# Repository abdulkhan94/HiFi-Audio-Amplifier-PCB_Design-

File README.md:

# Transparent HiFi Audio Amplifier for Headphones
## Introduction
The goal of our Transparent HiFi USB Audio Amplifier system is to take in a audio signal via USB, allow the user to modify amplifier and volume controls, and to hear the modified audio signal through headphones. Our system specifications are for our design to not produce a DC offset that’s greater than 20mV, to not produce excessive power spikes greater than 50mV, have an output impedance of less than 2 ohms, and to support 8 specific headphones with a range of impedances from 16 to 600 ohms. The left and right audio signals must have flat frequency responses (+/-2.5dB), linear/flat phase responses without being set at 0dB, noise under -105dBv (-103dBu) and distortion under 1% THd into 150 ohms at 1Vrms. Lastly, the power amplifier must have a slew of under 3V/us by a square wave of 600 ohms. 

## Power Amplifier
The power amplifier subsystem will get a 1 V pk-pk signal input from the Amplifier controls subsystem and will amplify that to output analog audio signal across various headphones. All parts of the subsystem will be powered by +13/-13 DC Voltage signal. The subsystem consists of two different parts to achieve amplification of both current and voltage.
The first stage of the design consists of a preamplifier design. This is essentially a Class A audio amplifier which is implemented in order to boost the voltage of the 1 V pk-pk signal that the subsystem receives as input from the amplifier controls subsystem. A major design consideration that has been made here revolves around amplifying voltage to the adequate level while maintaining low noise in the signal. The design consists of two biasing resistors followed by a NPN transistor. This part of the design is powered by a +13V DC power rail. 
The next step of the design consists of the power amplifier which amplifies the current. This part of the subsystem is required to have enough current in order to drive the output across the headphones. A class AB amplifier design has been implemented here in order to achieve the adequate current amplification. This design also consists of two biasing resistors for each transistor and is powered by +/- 13V DC power rails.

## Current Status
* All subsytems of the design have been finalised and layed out on PCB's. 
* All subsystems integrated and fully functional.

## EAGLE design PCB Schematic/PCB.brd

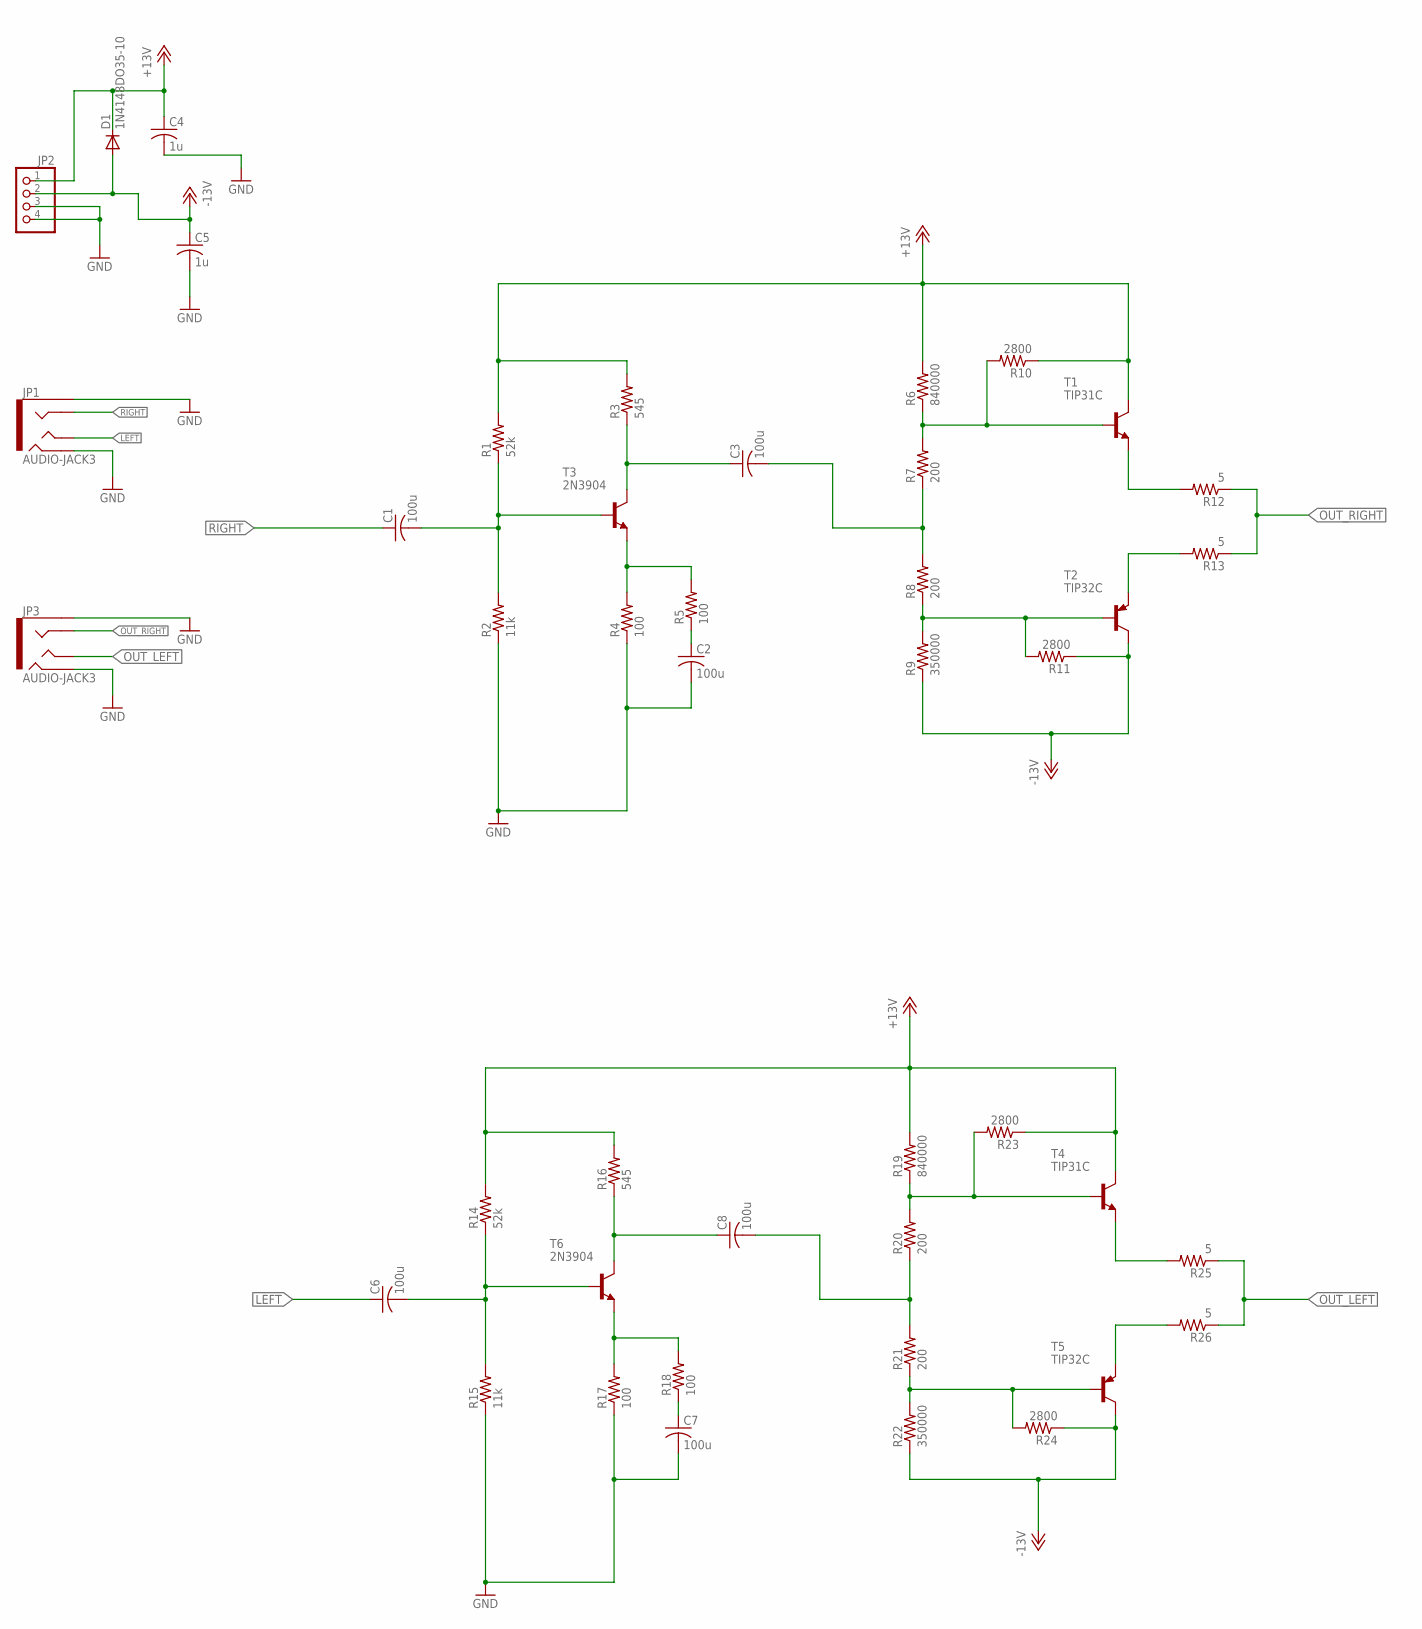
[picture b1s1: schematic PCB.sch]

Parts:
C1, C2, C3, C6, C7, C8: 100u; C025-024X044
C4, C5: 1u; C025-024X044
D1: 1N4148DO35-10; DO35-10
JP1, JP3: AUDIO-JACK3; AUDIO-JACK-TRRS-SMD
JP2: PINHD-1X4; 1X04
R1, R14: 52k; 0204V
R2, R15: 11k; 0204V
R3, R16: 545; 0204V
R4, R5, R17, R18: 100; 0204V
R6, R19: 840000; 0204V
R7, R8, R20, R21: 200; 0204V
R9, R22: 350000; 0204V
R10, R11, R23, R24: 2800; 0204V
R12, R13, R25, R26: 5; 0204V
T1, T4: TIP31C; TO220
T2, T5: TIP32C; TO220
T3, T6: 2N3904; TO92

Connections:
+13V: C4.1, D1.C, JP2.1, R1.2, R3.2, R6.2, R10.1, R14.2, R16.2, R19.2, R23.1, T1.2 (C), T4.2 (C)
-13V: C5.1, D1.A, JP2.2, R9.1, R11.1, R22.1, R24.1, T2.2 (C), T5.2 (C)
GND: C2.2, C4.2, C5.2, C7.2, JP1.EARTH, JP1.RING2, JP2.3, JP2.4, JP3.EARTH, JP3.RING2, R2.1, R4.1, R15.1, R17.1
LEFT: C6.1, JP1.TIP
unnamed: C1.2, R1.1, R2.2, T3.2 (B)
unnamed: C3.1, R3.1, T3.1 (C)
unnamed: C6.2, R14.1, R15.2, T6.2 (B)
unnamed: R4.2, R5.2, T3.3 (E)
unnamed: R6.1, R7.2, R10.2, T1.1 (B)
unnamed: C2.1, R5.1
unnamed: C3.2, R7.1, R8.2
unnamed: R8.1, R9.2, R11.2, T2.1 (B)
unnamed: R12.2, T1.3 (E)
unnamed: R13.2, T2.3 (E)
unnamed: C8.1, R16.1, T6.1 (C)
unnamed: R17.2, R18.2, T6.3 (E)
unnamed: C7.1, R18.1
unnamed: R19.1, R20.2, R23.2, T4.1 (B)
unnamed: C8.2, R20.1, R21.2
unnamed: R21.1, R22.2, R24.2, T5.1 (B)
unnamed: R25.2, T4.3 (E)
unnamed: R26.2, T5.3 (E)
OUT_LEFT: JP3.TIP, R25.1, R26.1
OUT_RIGHT: JP3.RING1, R12.1, R13.1
RIGHT: C1.1, JP1.RING1

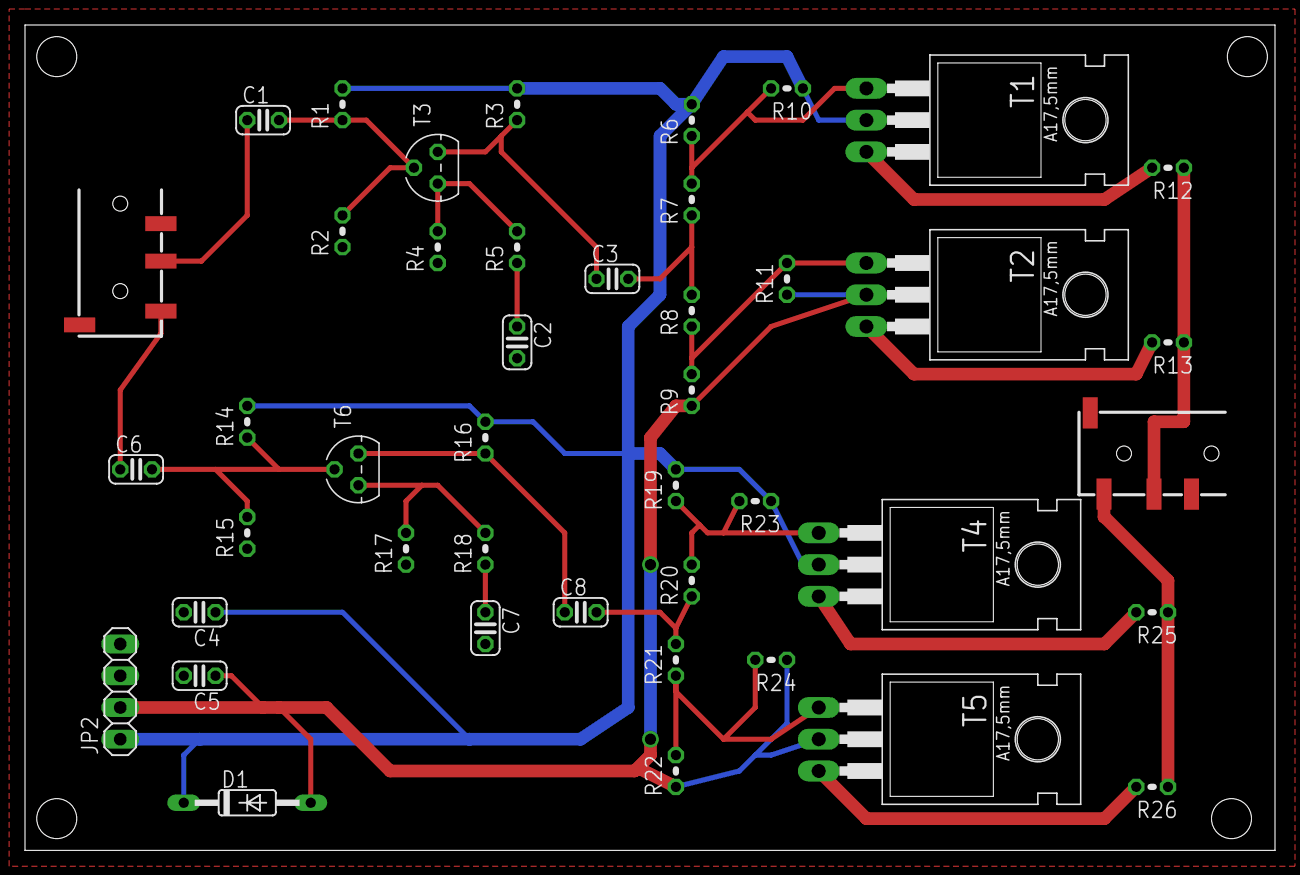
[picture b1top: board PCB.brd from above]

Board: 2 copper layers, 100.0 x 66.0 mm, 44 parts (0 on the bottom side), 25 nets.

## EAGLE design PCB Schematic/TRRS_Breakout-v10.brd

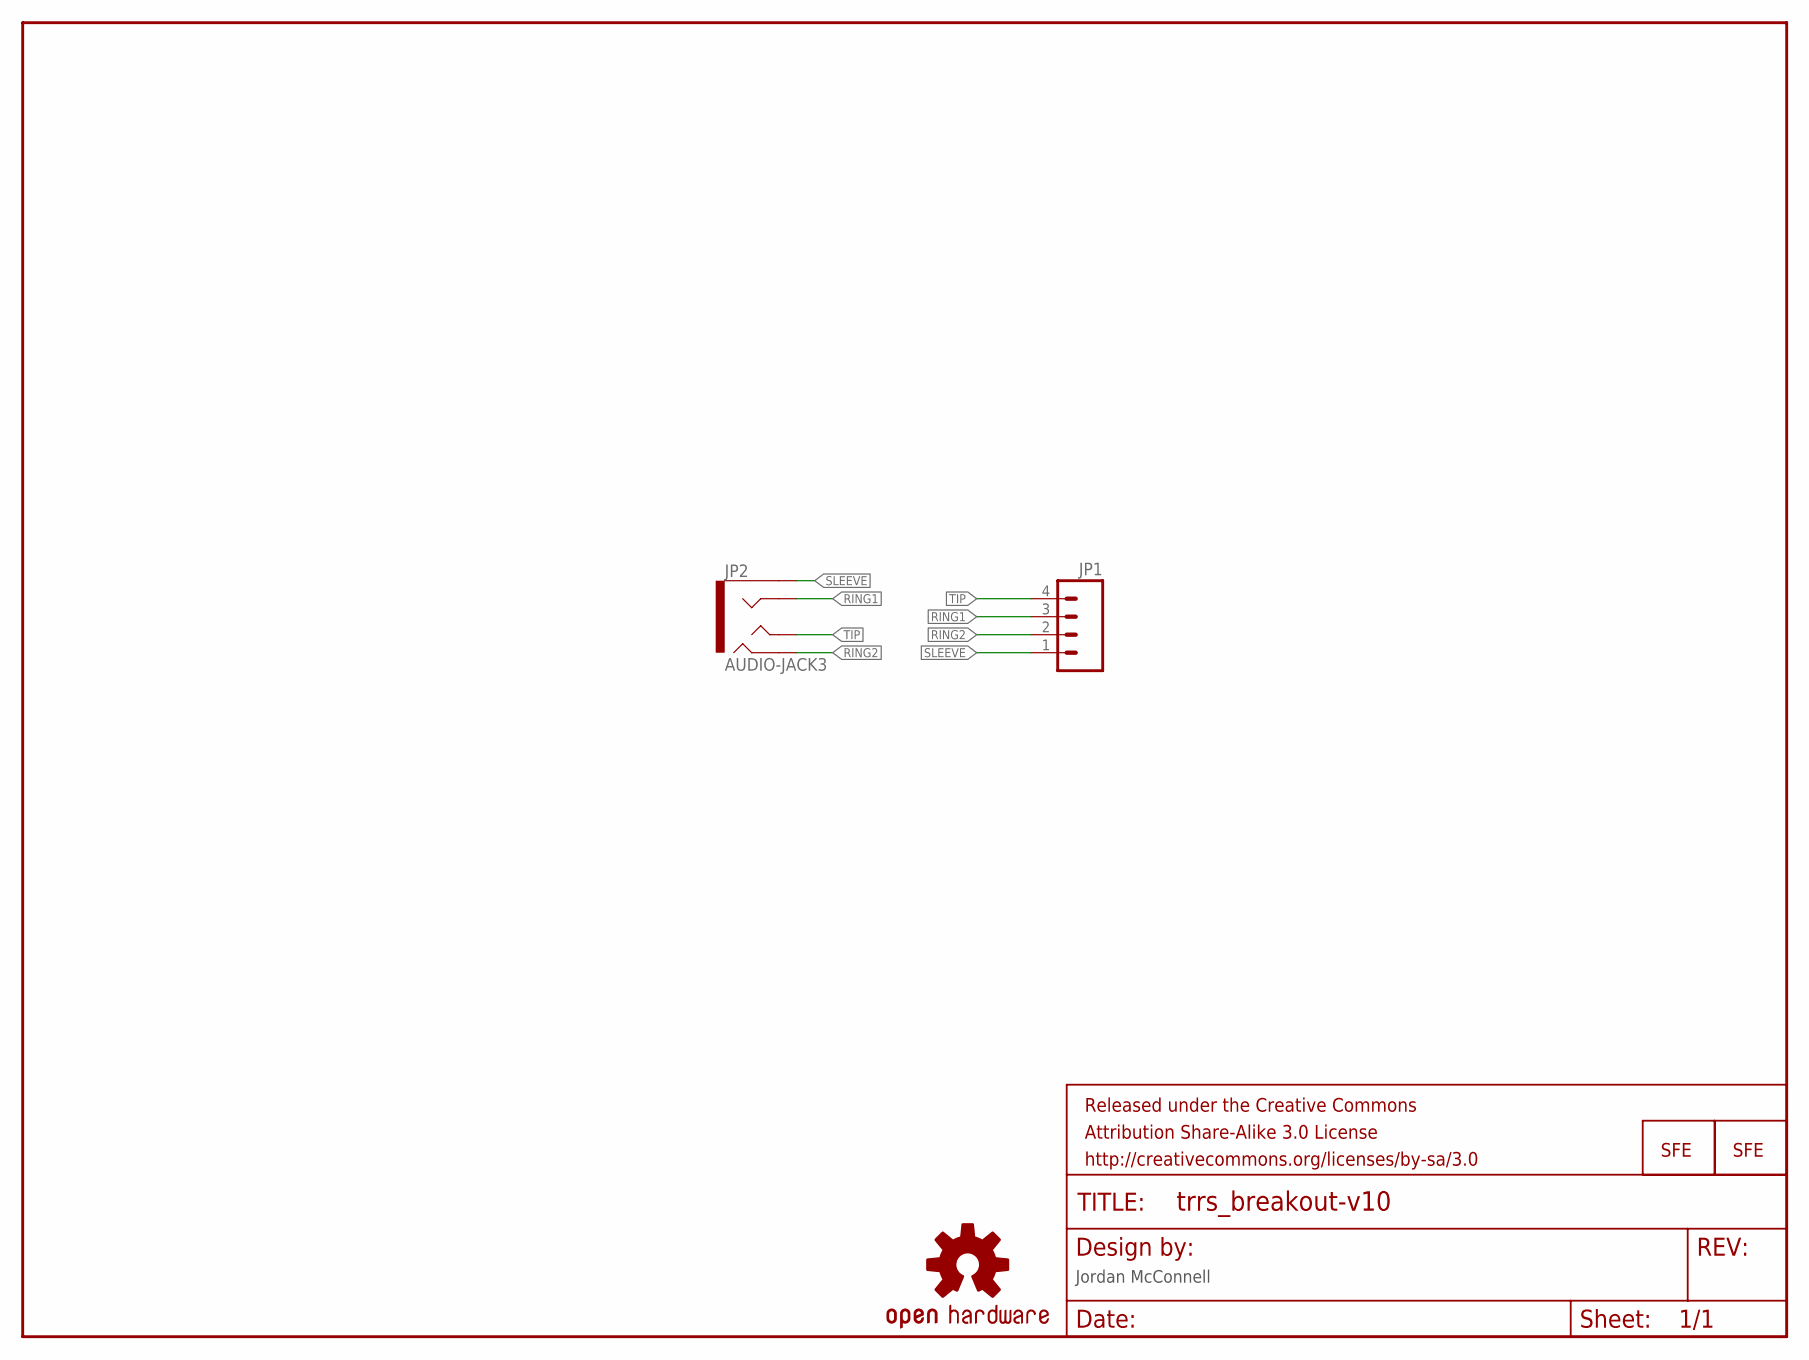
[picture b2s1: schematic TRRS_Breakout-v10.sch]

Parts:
FRAME1: FRAME-LETTER; CREATIVE_COMMONS
JP1: M04PTH; 1X04
JP2: AUDIO-JACK3; AUDIO-JACK-TRRS-SMD
JP3, JP4: LOGO-SFESK; SFE-LOGO-FLAME
U$1: OSHW-LOGOS; OSHW-LOGO-S

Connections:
RING1: JP1.3, JP2.RING1
RING2: JP1.2, JP2.RING2
SLEEVE: JP1.1, JP2.EARTH
TIP: JP1.4, JP2.TIP

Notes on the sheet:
Jordan McConnell

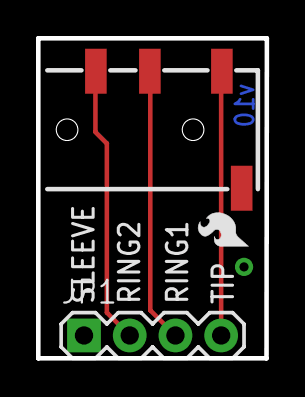
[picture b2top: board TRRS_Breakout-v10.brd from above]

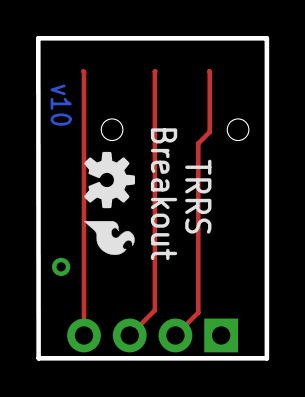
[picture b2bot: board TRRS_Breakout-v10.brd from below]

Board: 2 copper layers, 12.7 x 17.8 mm, 6 parts (2 on the bottom side), 4 nets.

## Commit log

2017-05-23 Senior Design
    USB Hi-fi Audio amplifier

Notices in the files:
parts and their libraries:
SparkFun-Connectors: Licensing: CC v3.0 Share-Alike You are welcome to use this library for commercial purposes.
SparkFun-Aesthetics: Released under the Creative Commons Attribution Share-Alike 3.0 License
SparkFun-Aesthetics: http://creativecommons.org/licenses/by-sa/3.0
